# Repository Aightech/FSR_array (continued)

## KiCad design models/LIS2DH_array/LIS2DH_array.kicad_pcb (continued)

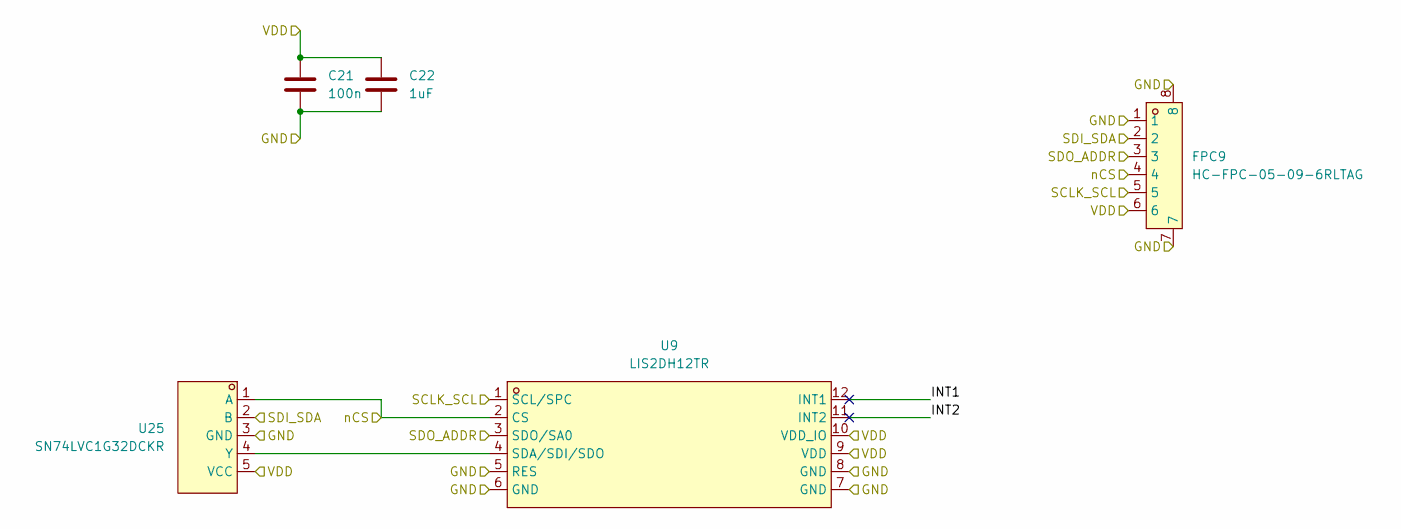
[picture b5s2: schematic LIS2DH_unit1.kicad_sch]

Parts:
C21: 100n; C_0402_1005Metric_Pad0.74x0.62mm_HandSolder; LCSC Part C1525
C22: 1uF; C_0402_1005Metric_Pad0.74x0.62mm_HandSolder; LCSC Part C52923
FPC9: HC-FPC-05-09-6RLTAG; FPC-SMD_6P-P0.50_HC-FPC-05-09-6RLTAG; LCSC Part C5213748
U9: LIS2DH12TR; LGA-12_L2.0-W2.0-P0.50-BL; LCSC Part C110926
U25: SN74LVC1G32DCKR; SOT-353_L2.1-W1.3-P0.65-LS2.3-BR; LCSC Part C7840

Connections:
/LIS2DH_unit9/INT1: U9.12 (INT1)
/LIS2DH_unit9/INT2: U9.11 (INT2)
GND: C21.2, C22.2, FPC9.1, FPC9.7, FPC9.8, U9.5 (RES), U9.6 (GND), U9.7 (GND), U9.8 (GND), U25.3 (GND); also elsewhere on the board
unnamed: U9.4 (SDA/SDI/SDO), U25.4 (Y)
SDI: FPC9.2, U25.2 (B); also elsewhere on the board
SDO: FPC9.3, U9.3 (SDO/SA0); also elsewhere on the board
Sclk: FPC9.5, U9.1 (SCL/SPC); also elsewhere on the board
VDD: C21.1, C22.1, FPC9.6, U9.9 (VDD), U9.10 (VDD_IO), U25.5 (VCC); also elsewhere on the board
nCS_9: FPC9.4, U9.2 (CS), U25.1 (A); also elsewhere on the board

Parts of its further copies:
C1, C3, C5, C7, C9, C11, C13, C15, C17, C19, C23, C25, C27, C29, C31: 100n; C_0402_1005Metric_Pad0.74x0.62mm_HandSolder; LCSC Part C1525
C2, C4, C6, C8, C10, C12, C14, C16, C18, C20, C24, C26, C28, C30, C32: 1uF; C_0402_1005Metric_Pad0.74x0.62mm_HandSolder; LCSC Part C52923
FPC1, FPC2, FPC3, FPC4, FPC5, FPC6, FPC7, FPC8, FPC10, FPC11, FPC12, FPC13, FPC14, FPC15, FPC16: HC-FPC-05-09-6RLTAG; FPC-SMD_6P-P0.50_HC-FPC-05-09-6RLTAG; LCSC Part C5213748
U1, U2, U3, U4, U5, U6, U7, U8, U10, U11, U12, U13, U14, U15, U16: LIS2DH12TR; LGA-12_L2.0-W2.0-P0.50-BL; LCSC Part C110926
U17, U18, U19, U20, U21, U22, U23, U24, U26, U27, U28, U29, U30, U31, U32: SN74LVC1G32DCKR; SOT-353_L2.1-W1.3-P0.65-LS2.3-BR; LCSC Part C7840

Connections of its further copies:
/LIS2DH_unit1/INT1: U1.12 (INT1)
/LIS2DH_unit1/INT2: U1.11 (INT2)
/LIS2DH_unit2/INT1: U2.12 (INT1)
/LIS2DH_unit2/INT2: U2.11 (INT2)
/LIS2DH_unit3/INT1: U3.12 (INT1)
/LIS2DH_unit3/INT2: U3.11 (INT2)
/LIS2DH_unit4/INT1: U4.12 (INT1)
/LIS2DH_unit4/INT2: U4.11 (INT2)
/LIS2DH_unit5/INT1: U5.12 (INT1)
/LIS2DH_unit5/INT2: U5.11 (INT2)
/LIS2DH_unit6/INT1: U6.12 (INT1)
/LIS2DH_unit6/INT2: U6.11 (INT2)
/LIS2DH_unit7/INT1: U7.12 (INT1)
/LIS2DH_unit7/INT2: U7.11 (INT2)
/LIS2DH_unit8/INT1: U8.12 (INT1)
/LIS2DH_unit8/INT2: U8.11 (INT2)
/LIS2DH_unit10/INT1: U10.12 (INT1)
/LIS2DH_unit10/INT2: U10.11 (INT2)
/LIS2DH_unit11/INT1: U11.12 (INT1)
/LIS2DH_unit11/INT2: U11.11 (INT2)
/LIS2DH_unit12/INT1: U12.12 (INT1)
/LIS2DH_unit12/INT2: U12.11 (INT2)
/LIS2DH_unit13/INT1: U13.12 (INT1)
/LIS2DH_unit13/INT2: U13.11 (INT2)
/LIS2DH_unit14/INT1: U14.12 (INT1)
/LIS2DH_unit14/INT2: U14.11 (INT2)
/LIS2DH_unit15/INT1: U15.12 (INT1)
/LIS2DH_unit15/INT2: U15.11 (INT2)
/LIS2DH_unit16/INT1: U16.12 (INT1)
/LIS2DH_unit16/INT2: U16.11 (INT2)
GND: C1.2, C2.2, C3.2, C4.2, C5.2, C6.2, C7.2, C8.2, C9.2, C10.2, C11.2, C12.2, C13.2, C14.2, C15.2, C16.2, C17.2, C18.2, C19.2, C20.2, C23.2, C24.2, C25.2, C26.2, C27.2, C28.2, C29.2, C30.2, C31.2, C32.2, FPC1.1, FPC1.7, FPC1.8, FPC2.1, FPC2.7, FPC2.8, FPC3.1, FPC3.7, FPC3.8, FPC4.1, FPC4.7, FPC4.8, FPC5.1, FPC5.7, FPC5.8, FPC6.1, FPC6.7, FPC6.8, FPC7.1, FPC7.7, FPC7.8, FPC8.1, FPC8.7, FPC8.8, FPC10.1, FPC10.7, FPC10.8, FPC11.1, FPC11.7, FPC11.8, FPC12.1, FPC12.7, FPC12.8, FPC13.1, FPC13.7, FPC13.8, FPC14.1, FPC14.7, FPC14.8, FPC15.1, FPC15.7, FPC15.8, FPC16.1, FPC16.7, FPC16.8, U1.5 (RES), U1.6 (GND), U1.7 (GND), U1.8 (GND), U2.5 (RES), U2.6 (GND), U2.7 (GND), U2.8 (GND), U3.5 (RES), U3.6 (GND), U3.7 (GND), U3.8 (GND), U4.5 (RES), U4.6 (GND), U4.7 (GND), U4.8 (GND), U5.5 (RES), U5.6 (GND), U5.7 (GND), U5.8 (GND), U6.5 (RES), U6.6 (GND), U6.7 (GND), U6.8 (GND), U7.5 (RES), U7.6 (GND), U7.7 (GND), U7.8 (GND), U8.5 (RES), U8.6 (GND), U8.7 (GND), U8.8 (GND), U10.5 (RES), U10.6 (GND), U10.7 (GND), U10.8 (GND), U11.5 (RES), U11.6 (GND), U11.7 (GND), U11.8 (GND), U12.5 (RES), U12.6 (GND), U12.7 (GND), U12.8 (GND), U13.5 (RES), U13.6 (GND), U13.7 (GND), U13.8 (GND), U14.5 (RES), U14.6 (GND), U14.7 (GND), U14.8 (GND), U15.5 (RES), U15.6 (GND), U15.7 (GND), U15.8 (GND), U16.5 (RES), U16.6 (GND), U16.7 (GND), U16.8 (GND), U17.3 (GND), U18.3 (GND), U19.3 (GND), U20.3 (GND), U21.3 (GND), U22.3 (GND), U23.3 (GND), U24.3 (GND), U26.3 (GND), U27.3 (GND), U28.3 (GND), U29.3 (GND), U30.3 (GND), U31.3 (GND), U32.3 (GND); also elsewhere on the board
unnamed: U1.4 (SDA/SDI/SDO), U17.4 (Y)
unnamed: U10.4 (SDA/SDI/SDO), U26.4 (Y)
unnamed: U11.4 (SDA/SDI/SDO), U27.4 (Y)
unnamed: U12.4 (SDA/SDI/SDO), U28.4 (Y)
unnamed: U13.4 (SDA/SDI/SDO), U29.4 (Y)
unnamed: U14.4 (SDA/SDI/SDO), U30.4 (Y)
unnamed: U15.4 (SDA/SDI/SDO), U31.4 (Y)
unnamed: U16.4 (SDA/SDI/SDO), U32.4 (Y)
unnamed: U2.4 (SDA/SDI/SDO), U18.4 (Y)
unnamed: U3.4 (SDA/SDI/SDO), U19.4 (Y)
unnamed: U4.4 (SDA/SDI/SDO), U20.4 (Y)
unnamed: U5.4 (SDA/SDI/SDO), U21.4 (Y)
unnamed: U6.4 (SDA/SDI/SDO), U22.4 (Y)
unnamed: U7.4 (SDA/SDI/SDO), U23.4 (Y)
unnamed: U8.4 (SDA/SDI/SDO), U24.4 (Y)
SDI: FPC1.2, FPC2.2, FPC3.2, FPC4.2, FPC5.2, FPC6.2, FPC7.2, FPC8.2, FPC10.2, FPC11.2, FPC12.2, FPC13.2, FPC14.2, FPC15.2, FPC16.2, U17.2 (B), U18.2 (B), U19.2 (B), U20.2 (B), U21.2 (B), U22.2 (B), U23.2 (B), U24.2 (B), U26.2 (B), U27.2 (B), U28.2 (B), U29.2 (B), U30.2 (B), U31.2 (B), U32.2 (B); also elsewhere on the board
SDO: FPC1.3, FPC2.3, FPC3.3, FPC4.3, FPC5.3, FPC6.3, FPC7.3, FPC8.3, FPC10.3, FPC11.3, FPC12.3, FPC13.3, FPC14.3, FPC15.3, FPC16.3, U1.3 (SDO/SA0), U2.3 (SDO/SA0), U3.3 (SDO/SA0), U4.3 (SDO/SA0), U5.3 (SDO/SA0), U6.3 (SDO/SA0), U7.3 (SDO/SA0), U8.3 (SDO/SA0), U10.3 (SDO/SA0), U11.3 (SDO/SA0), U12.3 (SDO/SA0), U13.3 (SDO/SA0), U14.3 (SDO/SA0), U15.3 (SDO/SA0), U16.3 (SDO/SA0); also elsewhere on the board
Sclk: FPC1.5, FPC2.5, FPC3.5, FPC4.5, FPC5.5, FPC6.5, FPC7.5, FPC8.5, FPC10.5, FPC11.5, FPC12.5, FPC13.5, FPC14.5, FPC15.5, FPC16.5, U1.1 (SCL/SPC), U2.1 (SCL/SPC), U3.1 (SCL/SPC), U4.1 (SCL/SPC), U5.1 (SCL/SPC), U6.1 (SCL/SPC), U7.1 (SCL/SPC), U8.1 (SCL/SPC), U10.1 (SCL/SPC), U11.1 (SCL/SPC), U12.1 (SCL/SPC), U13.1 (SCL/SPC), U14.1 (SCL/SPC), U15.1 (SCL/SPC), U16.1 (SCL/SPC); also elsewhere on the board
VDD: C1.1, C2.1, C3.1, C4.1, C5.1, C6.1, C7.1, C8.1, C9.1, C10.1, C11.1, C12.1, C13.1, C14.1, C15.1, C16.1, C17.1, C18.1, C19.1, C20.1, C23.1, C24.1, C25.1, C26.1, C27.1, C28.1, C29.1, C30.1, C31.1, C32.1, FPC1.6, FPC2.6, FPC3.6, FPC4.6, FPC5.6, FPC6.6, FPC7.6, FPC8.6, FPC10.6, FPC11.6, FPC12.6, FPC13.6, FPC14.6, FPC15.6, FPC16.6, U1.9 (VDD), U1.10 (VDD_IO), U2.9 (VDD), U2.10 (VDD_IO), U3.9 (VDD), U3.10 (VDD_IO), U4.9 (VDD), U4.10 (VDD_IO), U5.9 (VDD), U5.10 (VDD_IO), U6.9 (VDD), U6.10 (VDD_IO), U7.9 (VDD), U7.10 (VDD_IO), U8.9 (VDD), U8.10 (VDD_IO), U10.9 (VDD), U10.10 (VDD_IO), U11.9 (VDD), U11.10 (VDD_IO), U12.9 (VDD), U12.10 (VDD_IO), U13.9 (VDD), U13.10 (VDD_IO), U14.9 (VDD), U14.10 (VDD_IO), U15.9 (VDD), U15.10 (VDD_IO), U16.9 (VDD), U16.10 (VDD_IO), U17.5 (VCC), U18.5 (VCC), U19.5 (VCC), U20.5 (VCC), U21.5 (VCC), U22.5 (VCC), U23.5 (VCC), U24.5 (VCC), U26.5 (VCC), U27.5 (VCC), U28.5 (VCC), U29.5 (VCC), U30.5 (VCC), U31.5 (VCC), U32.5 (VCC); also elsewhere on the board
nCS_1: FPC1.4, U1.2 (CS), U17.1 (A); also elsewhere on the board
nCS_2: FPC2.4, U2.2 (CS), U18.1 (A); also elsewhere on the board
nCS_3: FPC3.4, U3.2 (CS), U19.1 (A); also elsewhere on the board
nCS_4: FPC4.4, U4.2 (CS), U20.1 (A); also elsewhere on the board
nCS_5: FPC5.4, U5.2 (CS), U21.1 (A); also elsewhere on the board
nCS_6: FPC6.4, U6.2 (CS), U22.1 (A); also elsewhere on the board
nCS_7: FPC7.4, U7.2 (CS), U23.1 (A); also elsewhere on the board
nCS_8: FPC8.4, U8.2 (CS), U24.1 (A); also elsewhere on the board
nCS_10: FPC10.4, U10.2 (CS), U26.1 (A); also elsewhere on the board
nCS_11: FPC11.4, U11.2 (CS), U27.1 (A); also elsewhere on the board
nCS_12: FPC12.4, U12.2 (CS), U28.1 (A); also elsewhere on the board
nCS_13: FPC13.4, U13.2 (CS), U29.1 (A); also elsewhere on the board
nCS_14: FPC14.4, U14.2 (CS), U30.1 (A); also elsewhere on the board
nCS_15: FPC15.4, U15.2 (CS), U31.1 (A); also elsewhere on the board
nCS_16: FPC16.4, U16.2 (CS), U32.1 (A); also elsewhere on the board

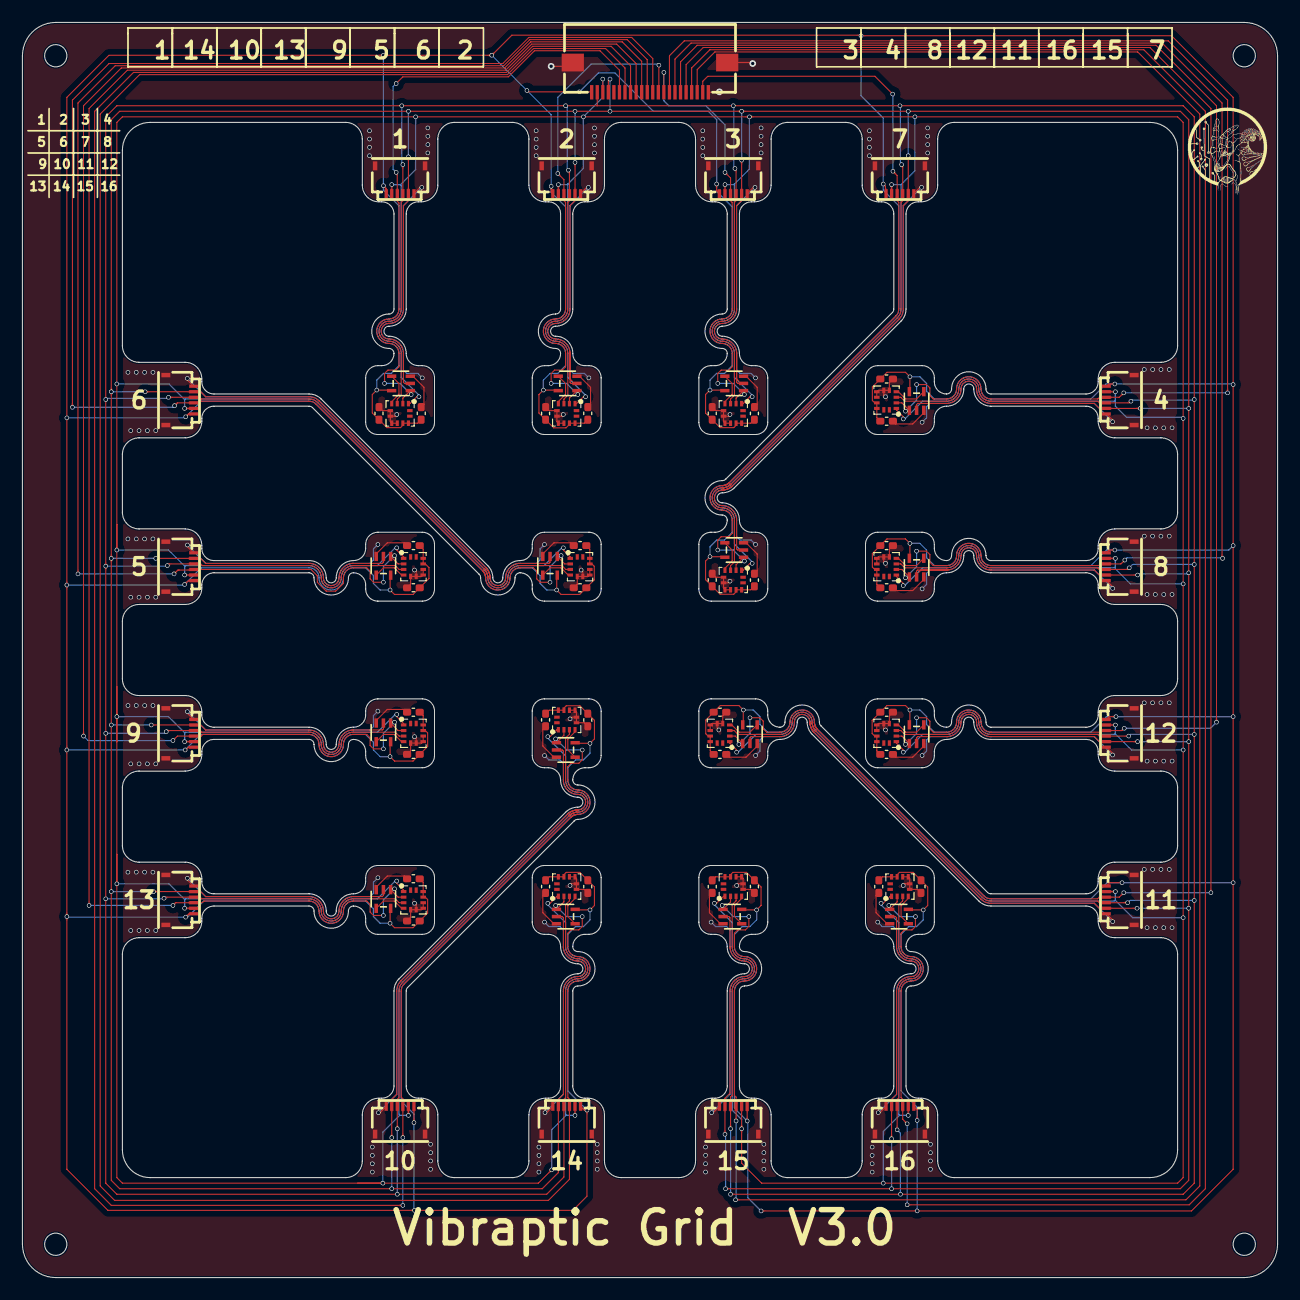
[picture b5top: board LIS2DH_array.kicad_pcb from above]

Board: 2 copper layers, 113.0 x 113.0 mm, 81 parts (0 on the bottom side), 37 nets.

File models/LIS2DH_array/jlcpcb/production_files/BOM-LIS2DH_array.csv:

Comment,Designator,Footprint,LCSC
LIS2DH12TR,"U1,U10,U11,U12,U13,U14,U15,U16,U2,U3,U4,U5,U6,U7,U8,U9",LGA-12_L2.0-W2.0-P0.50-BL,C110926
100n,"C1,C11,C13,C15,C17,C19,C21,C23,C25,C27,C29,C3,C31,C5,C7,C9",C_0402_1005Metric_Pad0.74x0.62mm_HandSolder,C1525
AFC01-S22FCA-00,FPC17,FPC-SMD_P0.5-22P_FGS-XJ-H2.0,C262668
HC-FPC-05-09-6RLTAG,"FPC1,FPC10,FPC11,FPC12,FPC13,FPC14,FPC15,FPC16,FPC2,FPC3,FPC4,FPC5,FPC6,FPC7,FPC8,FPC9",FPC-SMD_6P-P0.50_HC-FPC-05-09-6RLTAG,C5213748
1uF,"C10,C12,C14,C16,C18,C2,C20,C22,C24,C26,C28,C30,C32,C4,C6,C8",C_0402_1005Metric_Pad0.74x0.62mm_HandSolder,C52923
SN74LVC1G32DCKR,"U17,U18,U19,U20,U21,U22,U23,U24,U25,U26,U27,U28,U29,U30,U31,U32",SOT-353_L2.1-W1.3-P0.65-LS2.3-BR,C7840

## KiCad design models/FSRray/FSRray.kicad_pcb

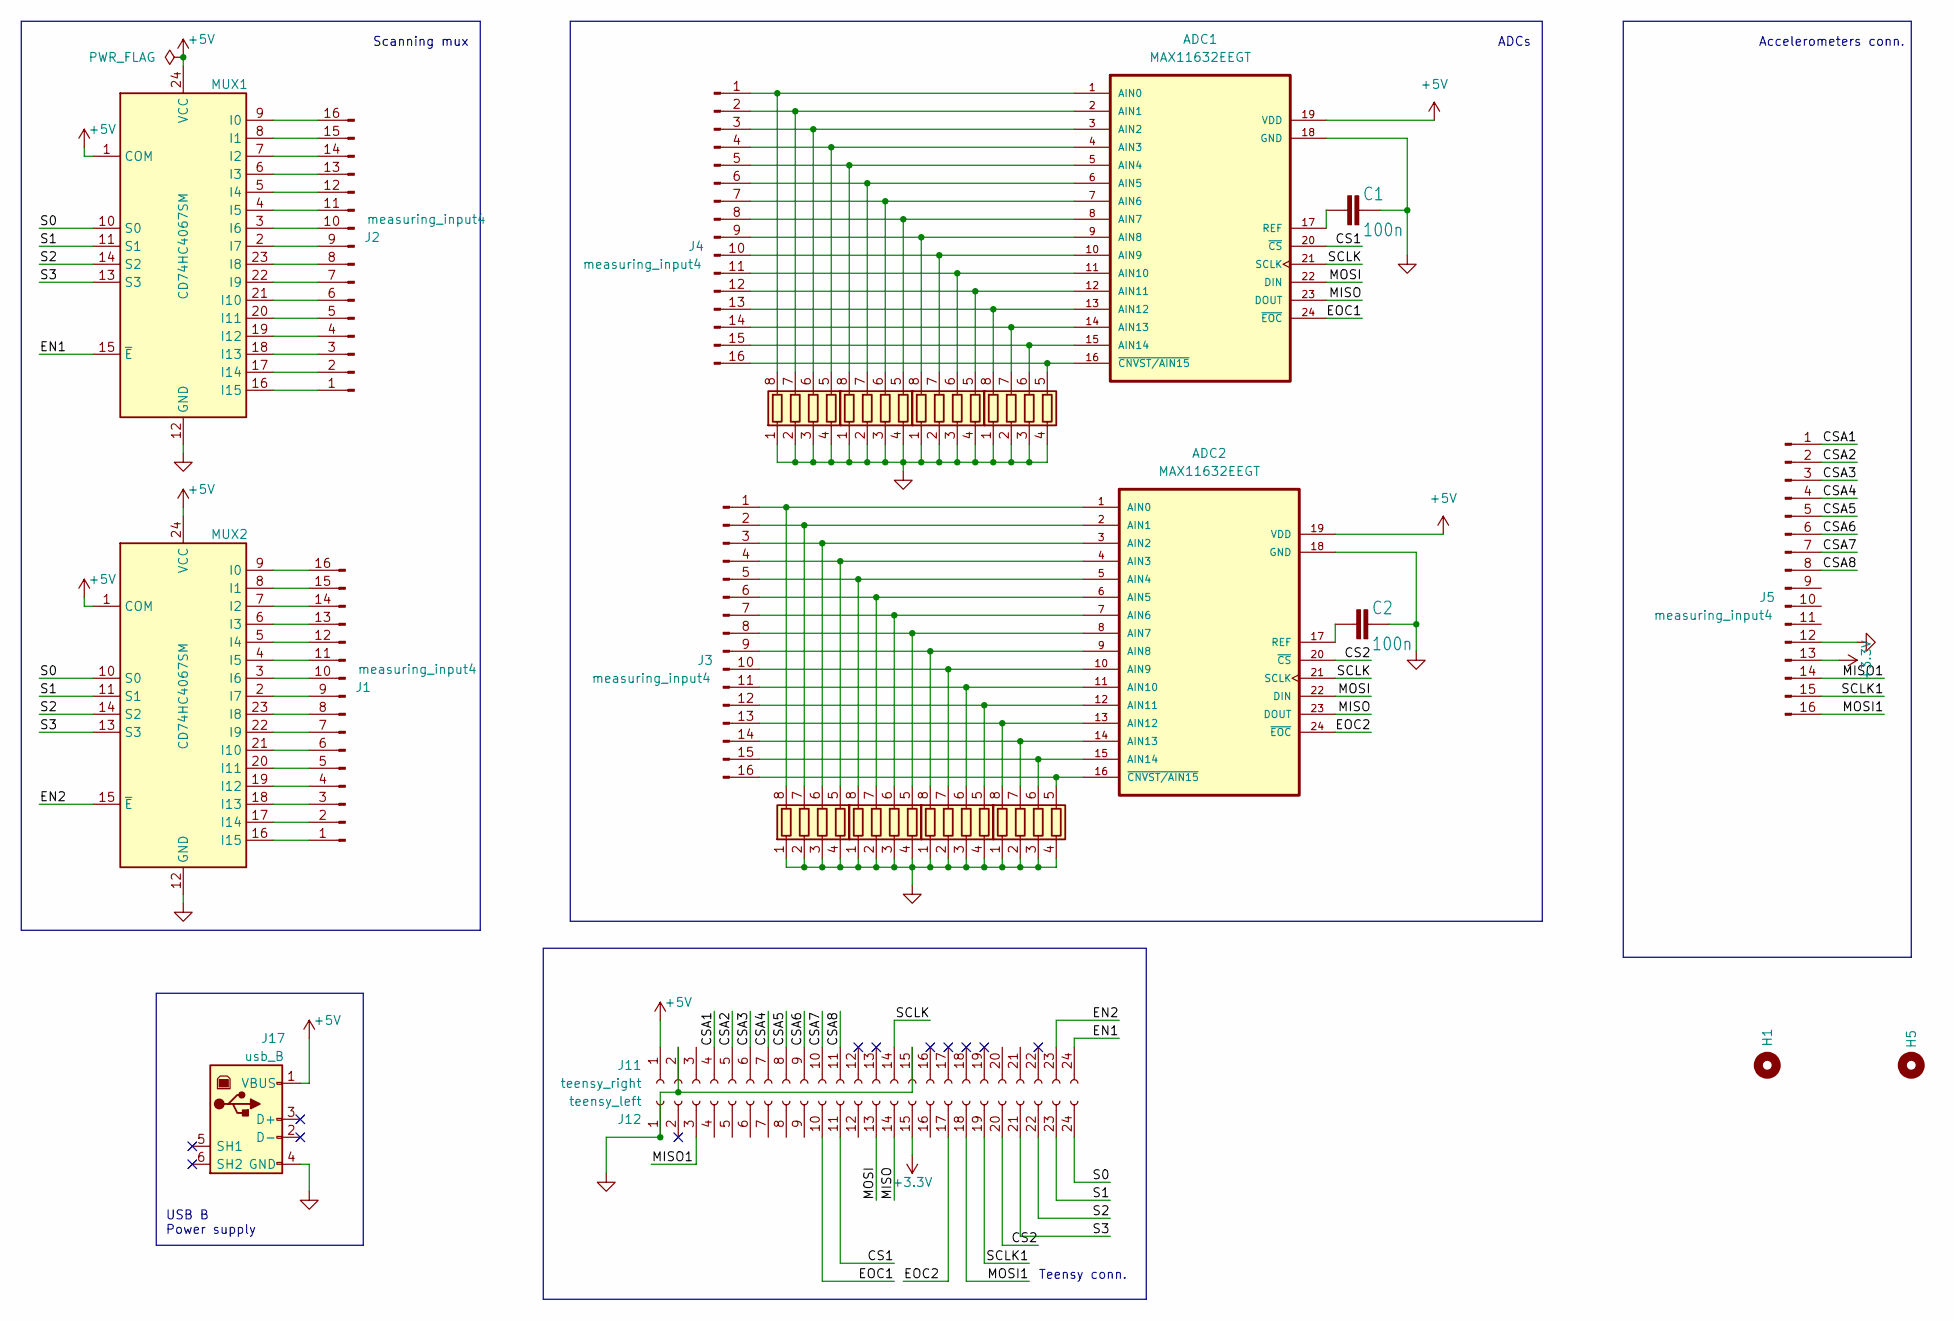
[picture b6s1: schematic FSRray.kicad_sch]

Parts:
ADC1, ADC2: MAX11632EEGT
C1, C2: 100n; C0603
H1, H5: MountingHole; MountingHole_3.2mm_M3
J1, J2, J3, J4, J5: measuring_input4; fcp_vertical_ULP94V0
J11: teensy_right; PinSocket_1x24_P2.54mm_Vertical
J12: teensy_left; PinSocket_1x24_P2.54mm_Vertical
J17: usb_B; SS52300001; Mouser Part Number 530-SS-52300-001
MUX1, MUX2: CD74HC4067SM; SSOP-24_5.3x8.2mm_P0.65mm
RN1, RN2, RN3, RN4, RN5, RN6, RN7, RN8: R_Pack04; R_Array_Convex_4x0402

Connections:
+3.3V: J5.13, J12.15
+5V: ADC1.19 (VDD), ADC2.19 (VDD), J11.1, J17.1 (VBUS), MUX1.1 (COM), MUX1.24 (VCC), MUX2.1 (COM), MUX2.24 (VCC)
/CS1: ADC1.20 (~CS), J12.11
/CS2: ADC2.20 (~CS), J12.20
/CSA1: J5.1, J11.4
/CSA2: J5.2, J11.5
/CSA3: J5.3, J11.6
/CSA4: J5.4, J11.7
/CSA5: J5.5, J11.8
/CSA6: J5.6, J11.9
/CSA7: J5.7, J11.10
/CSA8: J5.8, J11.11
/EN1: J11.24, MUX1.15 (~E)
/EN2: J11.23, MUX2.15 (~E)
/EOC1: ADC1.24 (~EOC), J12.10
/EOC2: ADC2.24 (~EOC), J12.17
/MISO: ADC1.23 (DOUT), ADC2.23 (DOUT), J12.14
/MISO1: J5.14, J12.3
/MOSI: ADC1.22 (DIN), ADC2.22 (DIN), J12.13
/MOSI1: J5.16, J12.18
/S0: J12.24, MUX1.10 (S0), MUX2.10 (S0)
/S1: J12.23, MUX1.11 (S1), MUX2.11 (S1)
/S2: J12.22, MUX1.14 (S2), MUX2.14 (S2)
/S3: J12.21, MUX1.13 (S3), MUX2.13 (S3)
/SCLK: ADC1.21 (SCLK), ADC2.21 (SCLK), J11.14
/SCLK1: J5.15, J12.19
GND: ADC1.18 (GND), ADC2.18 (GND), C1.2, C2.2, J5.12, J11.2, J11.15, J12.1, J17.4 (GND), MUX1.12 (GND), MUX2.12 (GND), RN1.1 (R1.1), RN1.2 (R2.1), RN1.3 (R3.1), RN1.4 (R4.1), RN2.1 (R1.1), RN2.2 (R2.1), RN2.3 (R3.1), RN2.4 (R4.1), RN3.1 (R1.1), RN3.2 (R2.1), RN3.3 (R3.1), RN3.4 (R4.1), RN4.1 (R1.1), RN4.2 (R2.1), RN4.3 (R3.1), RN4.4 (R4.1), RN5.1 (R1.1), RN5.2 (R2.1), RN5.3 (R3.1), RN5.4 (R4.1), RN6.1 (R1.1), RN6.2 (R2.1), RN6.3 (R3.1), RN6.4 (R4.1), RN7.1 (R1.1), RN7.2 (R2.1), RN7.3 (R3.1), RN7.4 (R4.1), RN8.1 (R1.1), RN8.2 (R2.1), RN8.3 (R3.1), RN8.4 (R4.1)
unnamed: ADC1.1 (AIN0), J4.1, RN1.8 (R1.2)
unnamed: ADC1.2 (AIN1), J4.2, RN1.7 (R2.2)
unnamed: ADC1.3 (AIN2), J4.3, RN1.6 (R3.2)
unnamed: ADC1.4 (AIN3), J4.4, RN1.5 (R4.2)
unnamed: ADC1.5 (AIN4), J4.5, RN2.8 (R1.2)
unnamed: ADC1.6 (AIN5), J4.6, RN2.7 (R2.2)
unnamed: ADC1.7 (AIN6), J4.7, RN2.6 (R3.2)
unnamed: ADC1.8 (AIN7), J4.8, RN2.5 (R4.2)
unnamed: ADC1.9 (AIN8), J4.9, RN3.8 (R1.2)
unnamed: ADC1.10 (AIN9), J4.10, RN3.7 (R2.2)
unnamed: ADC1.11 (AIN10), J4.11, RN3.6 (R3.2)
unnamed: ADC1.12 (AIN11), J4.12, RN3.5 (R4.2)
unnamed: ADC1.13 (AIN12), J4.13, RN4.8 (R1.2)
unnamed: ADC1.14 (AIN13), J4.14, RN4.7 (R2.2)
unnamed: ADC1.15 (AIN14), J4.15, RN4.6 (R3.2)
unnamed: ADC1.17 (REF), C1.1
unnamed: ADC1.16 (~CNVST/AIN15), J4.16, RN4.5 (R4.2)
unnamed: ADC2.1 (AIN0), J3.1, RN5.8 (R1.2)
unnamed: ADC2.2 (AIN1), J3.2, RN5.7 (R2.2)
unnamed: ADC2.3 (AIN2), J3.3, RN5.6 (R3.2)
unnamed: ADC2.4 (AIN3), J3.4, RN5.5 (R4.2)
unnamed: ADC2.5 (AIN4), J3.5, RN6.8 (R1.2)
unnamed: ADC2.6 (AIN5), J3.6, RN6.7 (R2.2)
unnamed: ADC2.7 (AIN6), J3.7, RN6.6 (R3.2)
unnamed: ADC2.8 (AIN7), J3.8, RN6.5 (R4.2)
unnamed: ADC2.9 (AIN8), J3.9, RN7.8 (R1.2)
unnamed: ADC2.10 (AIN9), J3.10, RN7.7 (R2.2)
unnamed: ADC2.11 (AIN10), J3.11, RN7.6 (R3.2)
unnamed: ADC2.12 (AIN11), J3.12, RN7.5 (R4.2)
unnamed: ADC2.13 (AIN12), J3.13, RN8.8 (R1.2)
unnamed: ADC2.14 (AIN13), J3.14, RN8.7 (R2.2)
unnamed: ADC2.15 (AIN14), J3.15, RN8.6 (R3.2)
unnamed: ADC2.17 (REF), C2.1
unnamed: ADC2.16 (~CNVST/AIN15), J3.16, RN8.5 (R4.2)
unnamed: J1.1, MUX2.16 (I15)
unnamed: J1.2, MUX2.17 (I14)
unnamed: J1.3, MUX2.18 (I13)
unnamed: J1.4, MUX2.19 (I12)
unnamed: J1.5, MUX2.20 (I11)
unnamed: J1.6, MUX2.21 (I10)
unnamed: J1.7, MUX2.22 (I9)
unnamed: J1.8, MUX2.23 (I8)
unnamed: J1.9, MUX2.2 (I7)
unnamed: J1.10, MUX2.3 (I6)
unnamed: J1.11, MUX2.4 (I5)
unnamed: J1.12, MUX2.5 (I4)
unnamed: J1.13, MUX2.6 (I3)
unnamed: J1.14, MUX2.7 (I2)
unnamed: J1.15, MUX2.8 (I1)
unnamed: J1.16, MUX2.9 (I0)
unnamed: J2.1, MUX1.16 (I15)
unnamed: J2.2, MUX1.17 (I14)
unnamed: J2.3, MUX1.18 (I13)
unnamed: J2.4, MUX1.19 (I12)
unnamed: J2.5, MUX1.20 (I11)
unnamed: J2.6, MUX1.21 (I10)
unnamed: J2.7, MUX1.22 (I9)
unnamed: J2.8, MUX1.23 (I8)
unnamed: J2.9, MUX1.2 (I7)
unnamed: J2.10, MUX1.3 (I6)
unnamed: J2.11, MUX1.4 (I5)
unnamed: J2.12, MUX1.5 (I4)
unnamed: J2.13, MUX1.6 (I3)
unnamed: J2.14, MUX1.7 (I2)
unnamed: J2.15, MUX1.8 (I1)
unnamed: J2.16, MUX1.9 (I0)

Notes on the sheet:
ADCs
USB B Power supply
Accelerometers conn.
Teensy conn.
Scanning mux

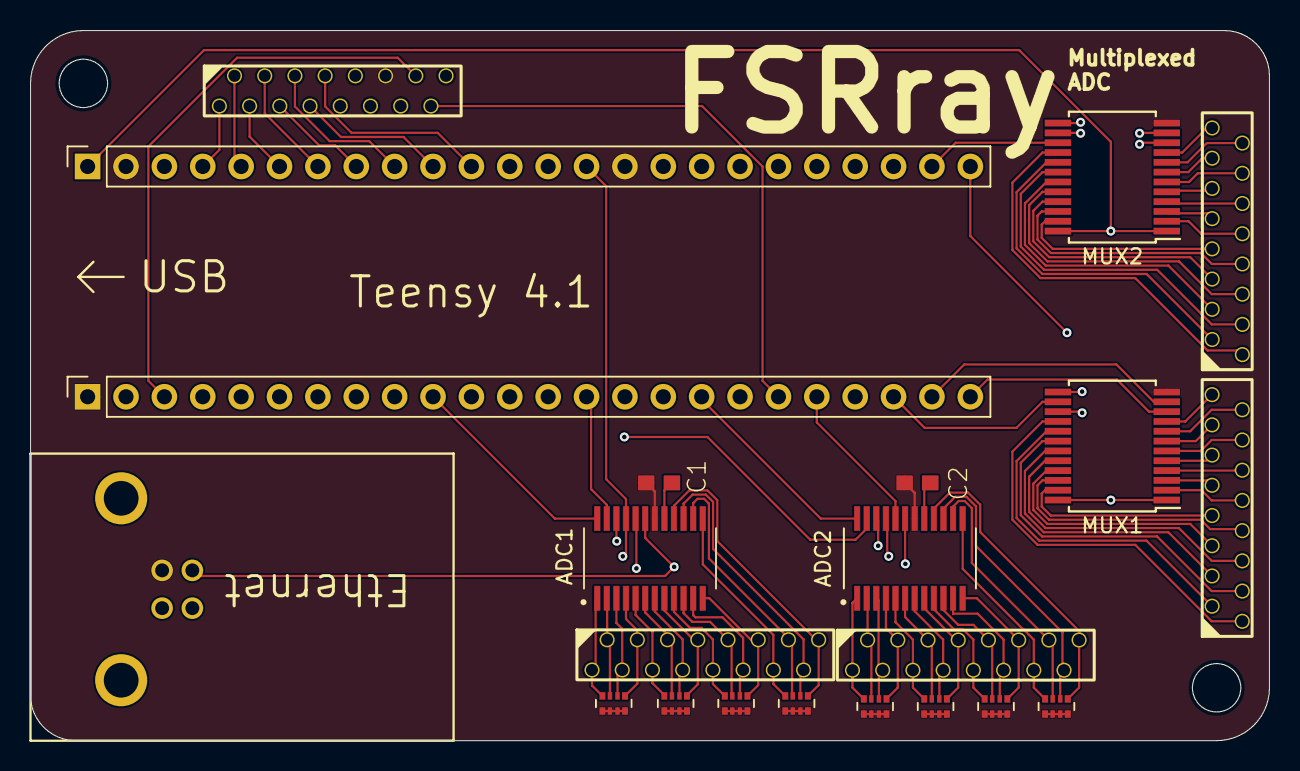
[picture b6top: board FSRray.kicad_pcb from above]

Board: 4 copper layers, 82.0 x 47.0 mm, 24 parts (1 on the bottom side), 93 nets.

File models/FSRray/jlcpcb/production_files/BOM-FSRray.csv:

Comment,Designator,Footprint,LCSC
R_Pack04,RN5,R_Array_Convex_4x0402,
MountingHole,H5,MountingHole_3.2mm_M3,
measuring_input4,J2,fcp_vertical_ULP94V0,
CD74HC4067SM,MUX2,SSOP-24_5.3x8.2mm_P0.65mm,
measuring_input4,J3,fcp_vertical_ULP94V0,
CD74HC4067SM,MUX1,SSOP-24_5.3x8.2mm_P0.65mm,
MAX11632EEGT,ADC2,MAX11632EEGT,
R_Pack04,RN6,R_Array_Convex_4x0402,
measuring_input4,J5,fcp_vertical_ULP94V0,
measuring_input4,J1,fcp_vertical_ULP94V0,
R_Pack04,RN1,R_Array_Convex_4x0402,
measuring_input4,J4,fcp_vertical_ULP94V0,
MountingHole,H1,MountingHole_3.2mm_M3,
R_Pack04,RN4,R_Array_Convex_4x0402,
100n,C1,C0603,
R_Pack04,RN2,R_Array_Convex_4x0402,
teensy_left,J12,PinSocket_1x24_P2.54mm_Vertical,
R_Pack04,RN7,R_Array_Convex_4x0402,
MAX11632EEGT,ADC1,MAX11632EEGT,
100n,C2,C0603,
R_Pack04,RN8,R_Array_Convex_4x0402,
R_Pack04,RN3,R_Array_Convex_4x0402,
teensy_right,J11,PinSocket_1x24_P2.54mm_Vertical,
usb_B,J17,usbB_stewart,

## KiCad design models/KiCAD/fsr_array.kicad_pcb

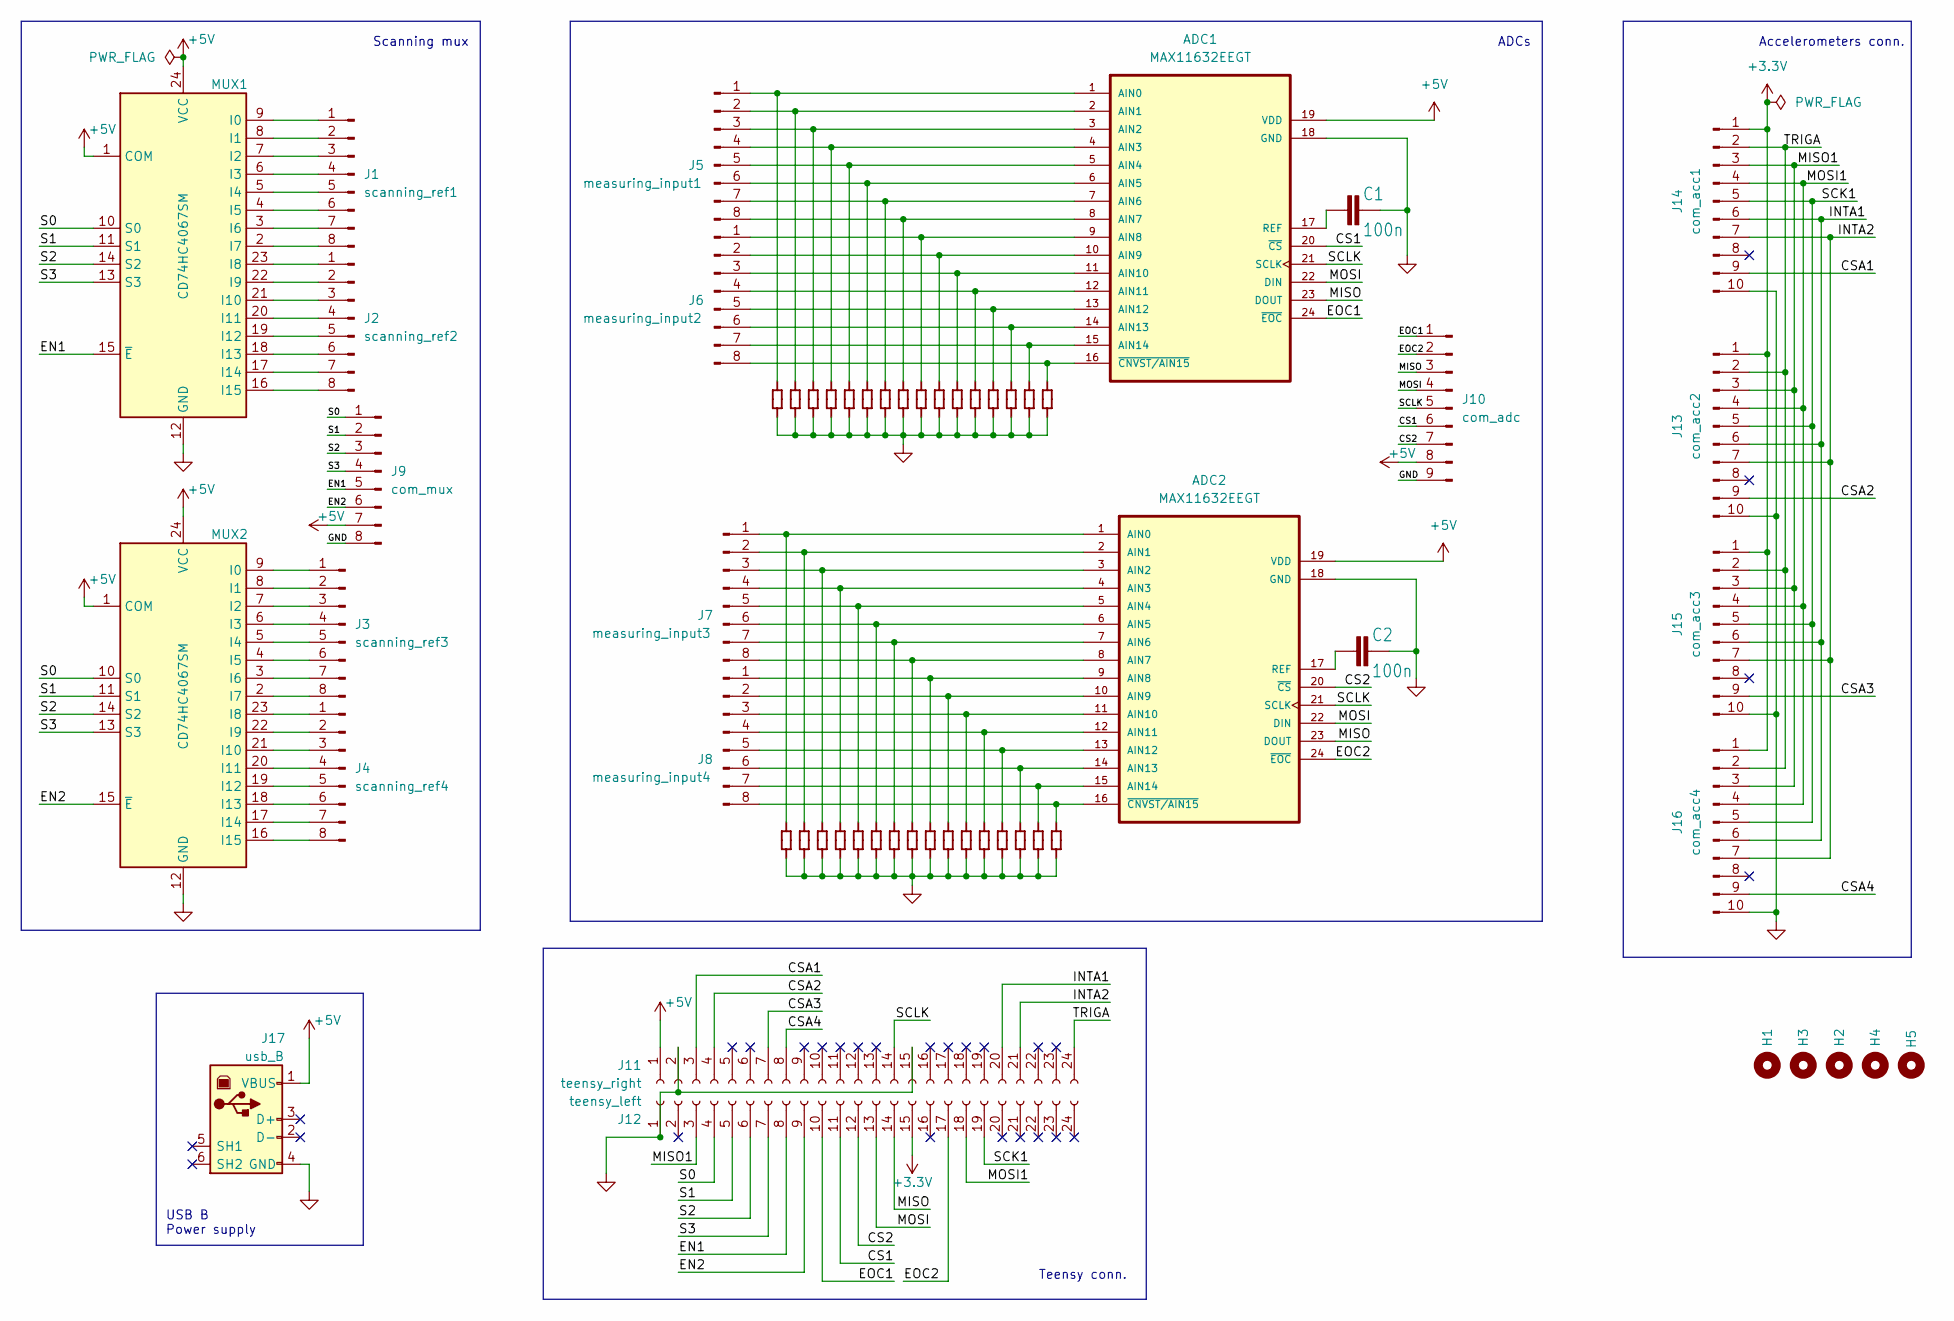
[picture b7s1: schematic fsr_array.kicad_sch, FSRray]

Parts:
ADC1, ADC2: MAX11632EEGT
C1, C2: 100n; C0603
H1, H2, H3, H4, H5: MountingHole; MountingHole_3.2mm_M3
J1: scanning_ref1; PinHeader_1x08_P2.54mm_Vertical
J2: scanning_ref2; PinHeader_1x08_P2.54mm_Vertical
J3: scanning_ref3; PinHeader_1x08_P2.54mm_Vertical
J4: scanning_ref4; PinHeader_1x08_P2.54mm_Vertical
J5: measuring_input1; PinHeader_1x08_P2.54mm_Vertical
J6: measuring_input2; PinHeader_1x08_P2.54mm_Vertical
J7: measuring_input3; PinHeader_1x08_P2.54mm_Vertical
J8: measuring_input4; PinHeader_1x08_P2.54mm_Vertical
J9: com_mux; PinHeader_1x08_P2.54mm_Vertical
J10: com_adc; PinHeader_1x09_P2.54mm_Vertical
J11: teensy_right; PinSocket_1x24_P2.54mm_Vertical
J12: teensy_left; PinSocket_1x24_P2.54mm_Vertical
J13: com_acc2; PinHeader_2x05_P1.27mm_Vertical
J14: com_acc1; PinHeader_2x05_P1.27mm_Vertical
J15: com_acc3; PinHeader_2x05_P1.27mm_Vertical
J16: com_acc4; PinHeader_2x05_P1.27mm_Vertical
J17: usb_B; SS52300001; Mouser Part Number 530-SS-52300-001
MUX1, MUX2: CD74HC4067SM; SSOP-24_5.3x8.2mm_P0.65mm
U$1, U$2, U$3, U$4, U$5, U$6, U$7, U$8, U$9, U$10, U$11, U$12, U$13, U$14, U$15, U$16, U$17, U$18, U$19, U$20, U$21, U$22, U$23, U$24, U$25, U$26, U$27, U$28, U$29, U$30, U$31, U$32, U$33, U$34, U$35, U$36, U$37, U$38, U$39, U$40, U$41, U$42, U$43, U$44, U$45, U$46, U$47, U$48, U$49, U$50, U$51, U$52, U$53, U$54, U$55, U$56, U$57, U$58, U$59, U$60, U$61, U$62, U$63, U$64: HALF_RES; HALP_RES

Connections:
+3.3V: J12.15, J13.1, J14.1, J15.1, J16.1
/CS1: ADC1.20 (~CS), J10.6, J12.11
/CS2: ADC2.20 (~CS), J10.7, J12.12
/CSA1: J11.3, J14.9
/CSA2: J11.4, J13.9
/CSA3: J11.7, J15.9
/CSA4: J11.8, J16.9
/EN1: J9.5, J12.8, MUX1.15 (~E)
/EN2: J9.6, J12.9, MUX2.15 (~E)
/EOC1: ADC1.24 (~EOC), J10.1, J12.10
/EOC2: ADC2.24 (~EOC), J10.2, J12.17
/INTA1: J11.20, J13.6, J14.6, J15.6, J16.6
/INTA2: J11.21, J13.7, J14.7, J15.7, J16.7
/L2: J17.2
/L3: J17.3
/M1: J17.MH1
/M2: J17.MH2
/MISO: ADC1.23 (DOUT), ADC2.23 (DOUT), J10.3, J12.14
/MISO1: J12.3, J13.3, J14.3, J15.3, J16.3
/MOSI: ADC1.22 (DIN), ADC2.22 (DIN), J10.4, J12.13
/MOSI1: J12.18, J13.4, J14.4, J15.4, J16.4
/S0: J9.1, J12.4, MUX1.10 (S0), MUX2.10 (S0)
/S1: J9.2, J12.5, MUX1.11 (S1), MUX2.11 (S1)
/S2: J9.3, J12.6, MUX1.14 (S2), MUX2.14 (S2)
/S3: J9.4, J12.7, MUX1.13 (S3), MUX2.13 (S3)
/SCK1: J12.19, J13.5, J14.5, J15.5, J16.5
/SCLK: ADC1.21 (SCLK), ADC2.21 (SCLK), J10.5, J11.14
/TRIGA: J11.24, J13.2, J14.2, J15.2, J16.2
unnamed: ADC1.1 (AIN0), J5.1, U$16.P$1
unnamed: ADC1.2 (AIN1), J5.2, U$14.P$1
unnamed: ADC1.3 (AIN2), J5.3, U$12.P$1
unnamed: ADC1.4 (AIN3), J5.4, U$10.P$1
unnamed: ADC1.5 (AIN4), J5.5, U$8.P$1
unnamed: ADC1.6 (AIN5), J5.6, U$6.P$1
unnamed: ADC1.7 (AIN6), J5.7, U$4.P$1
unnamed: ADC1.8 (AIN7), J5.8, U$2.P$1
unnamed: ADC1.9 (AIN8), J6.1, U$32.P$1
unnamed: ADC1.10 (AIN9), J6.2, U$30.P$1
unnamed: ADC1.11 (AIN10), J6.3, U$28.P$1
unnamed: ADC1.12 (AIN11), J6.4, U$26.P$1
unnamed: ADC1.13 (AIN12), J6.5, U$24.P$1
unnamed: ADC1.14 (AIN13), J6.6, U$22.P$1
unnamed: ADC1.15 (AIN14), J6.7, U$20.P$1
unnamed: ADC1.17 (REF), C1.1
unnamed: ADC1.16 (~CNVST/AIN15), J6.8, U$18.P$1
unnamed: ADC2.1 (AIN0), J7.1, U$48.P$1
unnamed: ADC2.2 (AIN1), J7.2, U$46.P$1
unnamed: ADC2.3 (AIN2), J7.3, U$44.P$1
unnamed: ADC2.4 (AIN3), J7.4, U$42.P$1
unnamed: ADC2.5 (AIN4), J7.5, U$40.P$1
unnamed: ADC2.6 (AIN5), J7.6, U$38.P$1
unnamed: ADC2.7 (AIN6), J7.7, U$36.P$1
unnamed: ADC2.8 (AIN7), J7.8, U$34.P$1
unnamed: ADC2.9 (AIN8), J8.1, U$64.P$1
unnamed: ADC2.10 (AIN9), J8.2, U$62.P$1
unnamed: ADC2.11 (AIN10), J8.3, U$60.P$1
unnamed: ADC2.12 (AIN11), J8.4, U$58.P$1
unnamed: ADC2.13 (AIN12), J8.5, U$56.P$1
unnamed: ADC2.14 (AIN13), J8.6, U$54.P$1
unnamed: ADC2.15 (AIN14), J8.7, U$52.P$1
unnamed: ADC2.17 (REF), C2.1
unnamed: ADC2.16 (~CNVST/AIN15), J8.8, U$50.P$1
unnamed: J1.1, MUX1.9 (I0)
unnamed: J1.2, MUX1.8 (I1)
unnamed: J1.3, MUX1.7 (I2)
unnamed: J1.4, MUX1.6 (I3)
unnamed: J1.5, MUX1.5 (I4)
unnamed: J1.6, MUX1.4 (I5)
unnamed: J1.7, MUX1.3 (I6)
unnamed: J1.8, MUX1.2 (I7)
unnamed: J2.1, MUX1.23 (I8)
unnamed: J2.2, MUX1.22 (I9)
unnamed: J2.3, MUX1.21 (I10)
unnamed: J2.4, MUX1.20 (I11)
unnamed: J2.5, MUX1.19 (I12)
unnamed: J2.6, MUX1.18 (I13)
unnamed: J2.7, MUX1.17 (I14)
unnamed: J2.8, MUX1.16 (I15)
unnamed: J3.1, MUX2.9 (I0)
unnamed: J3.2, MUX2.8 (I1)
unnamed: J3.3, MUX2.7 (I2)
unnamed: J3.4, MUX2.6 (I3)
unnamed: J3.5, MUX2.5 (I4)
unnamed: J3.6, MUX2.4 (I5)
unnamed: J3.7, MUX2.3 (I6)
unnamed: J3.8, MUX2.2 (I7)
unnamed: J4.1, MUX2.23 (I8)
unnamed: J4.2, MUX2.22 (I9)
unnamed: J4.3, MUX2.21 (I10)
unnamed: J4.4, MUX2.20 (I11)
unnamed: J4.5, MUX2.19 (I12)
unnamed: J4.6, MUX2.18 (I13)
unnamed: J4.7, MUX2.17 (I14)
unnamed: J4.8, MUX2.16 (I15)

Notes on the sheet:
ADCs
USB B Power supply
Accelerometers conn.
Scanning mux
Teensy conn.

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
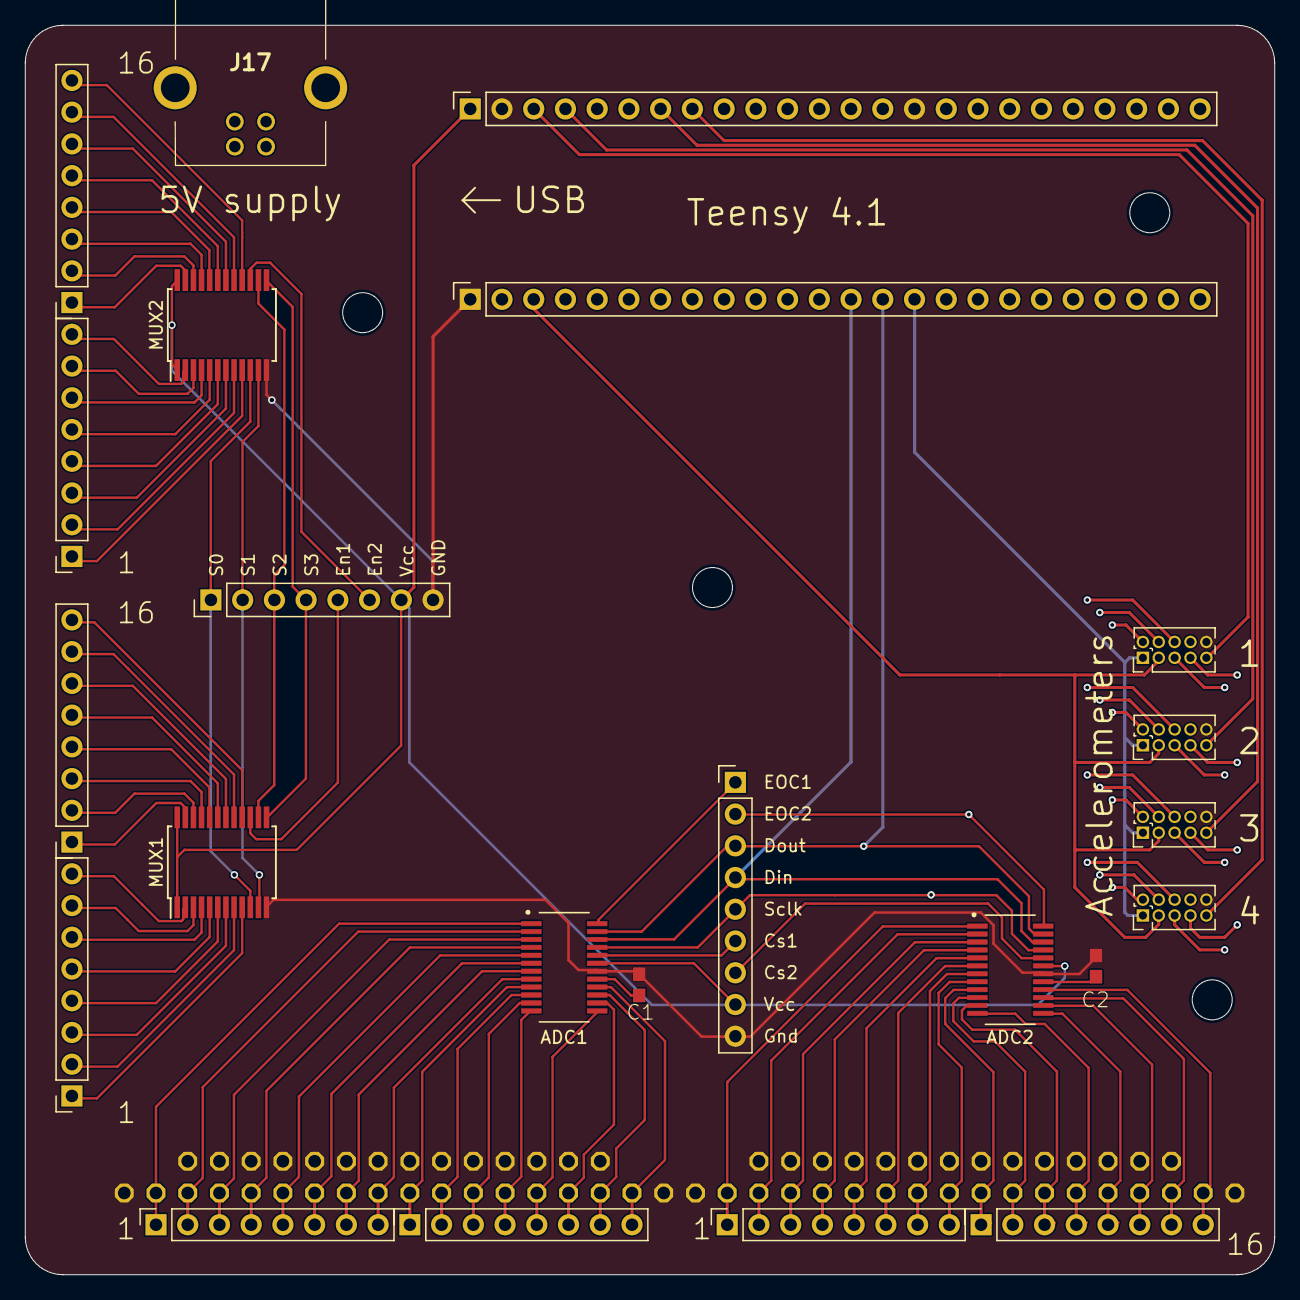
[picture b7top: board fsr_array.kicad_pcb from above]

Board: 4 copper layers, 100.0 x 100.0 mm, 92 parts (0 on the bottom side), 92 nets.

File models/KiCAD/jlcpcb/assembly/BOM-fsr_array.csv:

Comment,Designator,Footprint,LCSC
MAX11632EEGT,ADC1,MAX11632EEGT,
MAX11632EEGT,ADC2,MAX11632EEGT,
usb_B,J17,usbB_stewart,
MountingHole,H5,MountingHole_3.2mm_M3,
100n,C2,C0603,
measuring_input2,J6,PinHeader_1x08_P2.54mm_Vertical,
100n,C1,C0603,
scanning_ref4,J4,PinHeader_1x08_P2.54mm_Vertical,
MountingHole,H1,MountingHole_3.2mm_M3,
teensy_left,J12,PinSocket_1x24_P2.54mm_Vertical,
CD74HC4067SM,MUX2,SSOP-24_5.3x8.2mm_P0.65mm,
com_adc,J10,PinHeader_1x09_P2.54mm_Vertical,
scanning_ref1,J1,PinHeader_1x08_P2.54mm_Vertical,
com_acc1,J14,PinHeader_2x05_P1.27mm_Vertical,
scanning_ref3,J3,PinHeader_1x08_P2.54mm_Vertical,
com_acc2,J13,PinHeader_2x05_P1.27mm_Vertical,
MountingHole,H3,MountingHole_3.2mm_M3,
teensy_right,J11,PinSocket_1x24_P2.54mm_Vertical,
com_mux,J9,PinHeader_1x08_P2.54mm_Vertical,
measuring_input3,J7,PinHeader_1x08_P2.54mm_Vertical,
measuring_input4,J8,PinHeader_1x08_P2.54mm_Vertical,
MountingHole,H4,MountingHole_3.2mm_M3,
MountingHole,H2,MountingHole_3.2mm_M3,
com_acc4,J16,PinHeader_2x05_P1.27mm_Vertical,
com_acc3,J15,PinHeader_2x05_P1.27mm_Vertical,
measuring_input1,J5,PinHeader_1x08_P2.54mm_Vertical,
CD74HC4067SM,MUX1,SSOP-24_5.3x8.2mm_P0.65mm,
scanning_ref2,J2,PinHeader_1x08_P2.54mm_Vertical,
